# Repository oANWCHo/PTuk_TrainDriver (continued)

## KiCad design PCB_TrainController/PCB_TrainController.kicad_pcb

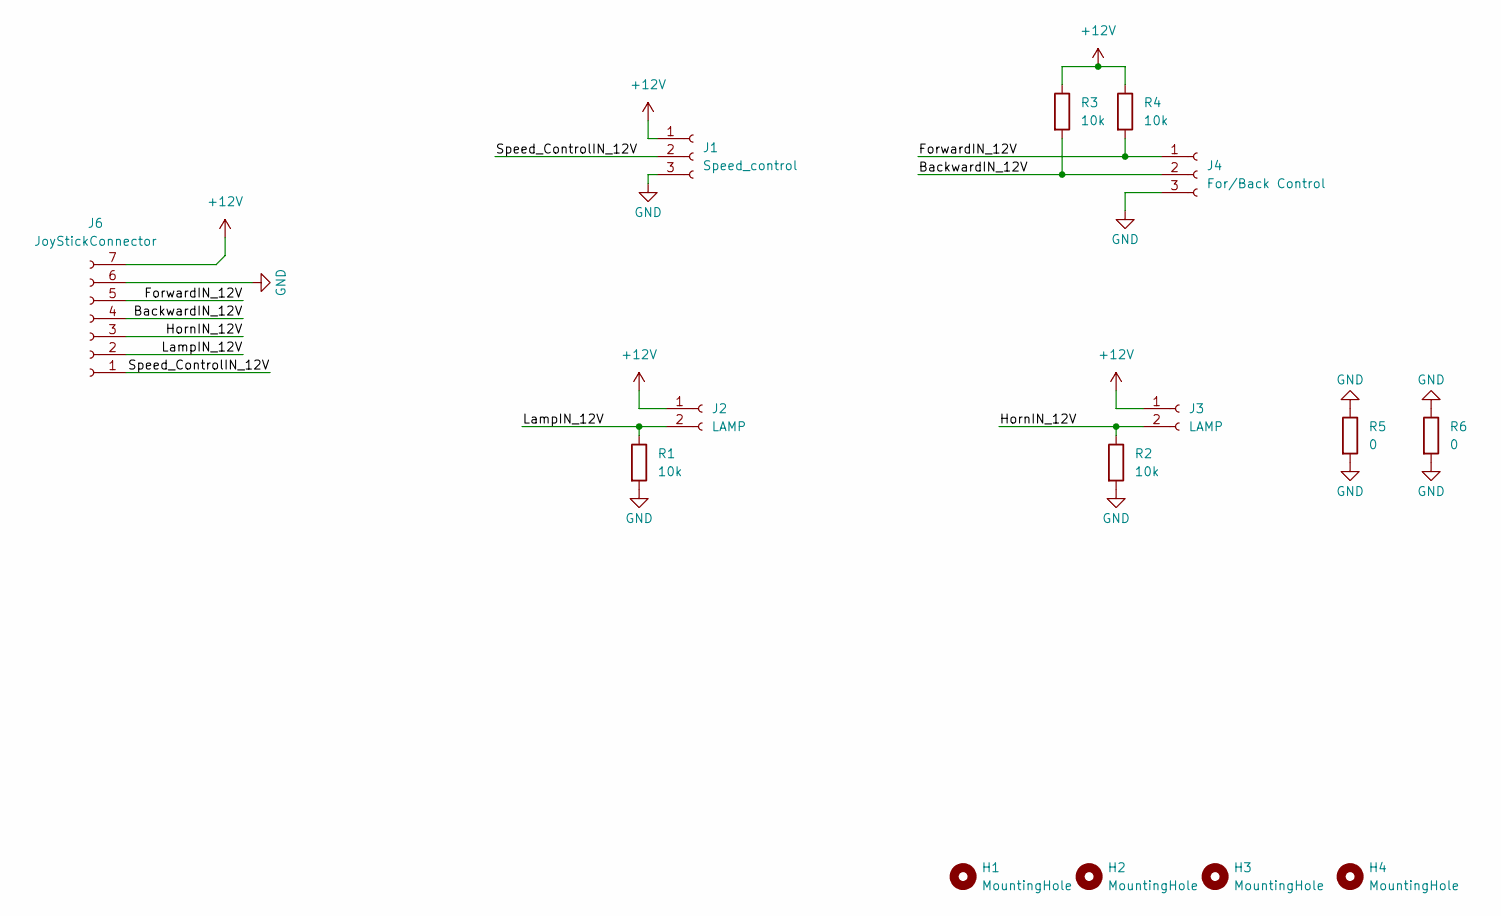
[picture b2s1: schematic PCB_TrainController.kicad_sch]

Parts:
H1, H2, H3, H4: MountingHole; MountingHole_3.2mm_M3_DIN965_Pad_TopBottom
J1: Speed_control; JST_XH_B3B-XH-A_1x03_P2.50mm_Vertical
J2, J3: LAMP; JST_XH_B2B-XH-A_1x02_P2.50mm_Vertical
J4: For/Back Control; JST_XH_B3B-XH-A_1x03_P2.50mm_Vertical
J6: JoyStickConnector; JST_XH_S7B-XH-A_1x07_P2.50mm_Horizontal
R1, R2, R3, R4: 10k; R_0805_2012Metric
R5, R6: 0; R_Axial_DIN0204_L3.6mm_D1.6mm_P5.08mm_Horizontal

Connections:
+12V: J1.1, J2.1, J3.1, J6.7, R3.1, R4.1
/BackwardIN_12V: J4.2, J6.4, R3.2
/ForwardIN_12V: J4.1, J6.5, R4.2
/HornIN_12V: J3.2, J6.3, R2.1
/LampIN_12V: J2.2, J6.2, R1.1
/Speed_ControlIN_12V: J1.2, J6.1
GND: J1.3, J4.3, J6.6, R1.2, R2.2, R5.1, R5.2, R6.1, R6.2

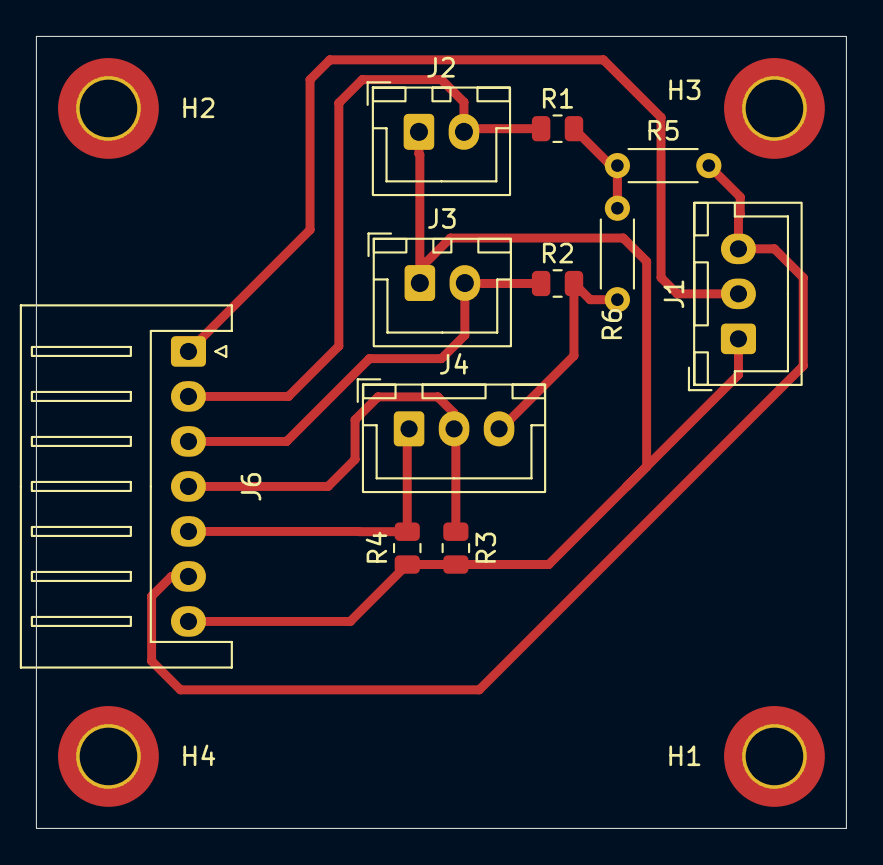
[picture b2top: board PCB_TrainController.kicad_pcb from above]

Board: 2 copper layers, 45.0 x 44.0 mm, 15 parts (0 on the bottom side), 7 nets.

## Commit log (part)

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2026-06-21 Finished MotorDriver and Aux pins
2026-06-21 Update_main_PCB
2026-06-27 Finished sch
2026-06-28 PCB Almost Finished
2026-06-28 Add aux led indicator
